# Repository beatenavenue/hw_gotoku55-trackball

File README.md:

English | [日本語](README_ja.md)

> They say the trackball journey ends once you buy a Kensington SlimBlade Pro and an Elecom COMFY wrist rest.  
> But couldn't the case be made smaller?

# GOTOKU-55 Trackball

## What is this?
This is a **"part"** for a 55 mm trackball. To see where it fits, you need some background, in order.

### Ploopy Adept
The Adept is a trackball with a 44 mm ball (1.75 in ≈ 44.5 mm), developed by Ploopy, a small Canadian company. The design files and firmware are open source, but parts you source yourself may not fit dimensionally, so buying a kit or a fully assembled unit from the official Ploopy store is recommended.

- Link: [Adept Trackball](https://ploopy.co/adept-trackball/)

### Anyball
Adept Anyball is a mod project that reworks the Adept case so that the ball rides on BTUs (ball transfer units). By choosing a case variant, you can use anything from a small 34 mm ball up to a 68 mm billiard ball. The files are published on GitHub, and you 3D print and assemble them yourself.

There is of course a 55 mm version, but its supports sit low, so the ball sticks far out of the case and it is not very comfortable to use.

- Link: [Adept Anyball](https://github.com/adept-anyball/)

### small-btu v4 (Slim)
A compact case for 34 mm / 38 mm balls by Fabricio Bastian, published within the Anyball project. It is made as low-profile as possible so that it can sit between the halves of a split keyboard, and its design is beautiful and refined.  
Going by the height of the buttons alone, it is probably lower than the Keychron Nape Pro, one of the smallest trackballs on the market. If you like low-profile keyboards, it is very appealing.

- Link: [adept-anyball/ploopy-adept-small-btu](https://github.com/adept-anyball/ploopy-adept-small-btu)

### GOTOKU-55
Putting a 55 mm ball on small-btu v4 is quite a stretch. The ball itself is large, and arms built for BTUs become huge as well, so it would be almost unusable.  
So, to keep things compact, I made an arm part (the "trackball support" in small-btu terms) that holds a 55 mm ball on the same ball bearings Ploopy uses. That is GOTOKU-55. The name comes from *gotoku* (五徳), the pronged trivet that holds a pot over a Japanese gas burner, which is what the arm part looks like. The 55 is the ball diameter in millimetres.

In most cases the arm part is all you need. The small-btu v4 case is polished and beautiful, so you can use it as is.

### The arm
There are two versions of the arm.

- **One-piece version.** For printing in PLA.
- **Split version.** For metal printing. The arm is metal, and the center floor (the cover over the sensor lens) is a separate PLA part.

A 55 mm ball is heavy, and you roll it with your palm. A PLA arm bends outward under this load. So I recommend printing the arm in metal with SLM (metal 3D printing, for example in stainless steel 316L). With a metal arm, the arm does not bend at all. A metal arm alone is enough to fix this problem.

Use the split version for metal printing. The PLA floor goes in from below. It is held between the metal arm and the sensor lens, so the heavy metal arm does not press on the lens.

### The case
However, with a grip like mine, the stock v4 gets in the way. When I lay my thumb flat to press the front buttons, the corner of the case hits my finger.

So, for people who hold it this way, I also made a modified case that extends the front buttons all the way to the edge.
The screw holes and so on are unchanged from v4, so printing only the top is enough. But the front wall disappears and it looks a little bare, so I made a bottom as well.

## Compatibility
small-btu v4 only.

The arm fits both the original small-btu v4 case and the GOTOKU case.

v5 has a similar shape, so it might work, but by my estimate the ball would probably interfere slightly.

## How to build
See the [build guide](docs/BUILD.md).

## License
Copyright (C) 2026 Kotaro WAJIKI  
Based on ploopy-adept-small-btu v4, Copyright (C) Fabricio Bastian  
Licensed under the GNU General Public License v3.0

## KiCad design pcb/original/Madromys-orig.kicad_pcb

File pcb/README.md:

English | [日本語](README_ja.md)

# GOTOKU PCB v1

This is a modified version of the Ploopy Madromys PCB (R1.001), the main board of the Ploopy Adept trackball.
The goal is to order the board with assembly (PCBA) from JLCPCB, so that no hand soldering is needed for the small parts.

**This is NOT an official Ploopy product. Do not ask Ploopy for support.**

This board is not built and not tested yet.

## This board alone is not a complete trackball

JLCPCB assembles all parts in the BOM except the optical sensor. You need to get these parts yourself and solder the sensor by hand.

- The optical sensor PMW3360DM-T2QU and the lens LM19-LSI

## Variants

There are two variants. They differ only in the USB-C connector.

| Folder | USB-C connector | Notes |
|---|---|---|
| [original](original/) | JAE DX07S016JA1R1500 (LCSC C3197885) | Same connector and routing as the original board. |
| [hro](hro/) | HRO TYPE-C-31-M-12 (LCSC C165948) | Slightly cheaper at JLCPCB. Routing around the connector was changed by hand. |

Each folder has these files:

- `*.kicad_pcb` is the board data for KiCad.
- `*-gerber.zip` is the Gerber and drill data.
- `*-BOM-JLC.csv` and `*-CPL-JLC.csv` are the BOM and the placement file for JLCPCB assembly.
- `*-gerber-preview.png` is a preview image of the Gerber data.

## Ordering at JLCPCB

- 4 layers, 0.8 mm thickness
- Assemble top side
- Upload the BOM and the CPL file of the same variant.

The optical sensor (PMW3360DM-T2QU) has no LCSC number in the BOM, so JLCPCB does not assemble it.

The package of the switch D2LS-21 (LCSC C3823622) is not listed on the JLCPCB part page. Check the position and the direction of the switches in the placement preview before you order.

## Changes from the original

The original data is the Altium project in [ploopyco/adept-trackball](https://github.com/ploopyco/adept-trackball) (`hardware/electronics/PCBs/Madromys`, commit `2ec4576`).
Only the PCB was converted. The schematic was not converted. See the original schematic PDF for the circuit.

### Conversion from Altium to KiCad

The board was converted with the Altium importer of KiCad 7.
These fixes were needed after the conversion.

- The square opening for the optical sensor is now a cutout in the board outline.
- The two locating holes of the USB-C connector are now non-plated holes.
- 10 very short broken arcs in the copper were replaced with straight segments.
- The board thickness is set to 0.8 mm. This value comes from the Altium layer stack.

### Parts that are not mounted

These parts are marked as "DNP" (do not populate). They are removed from the BOM and the CPL file. Their pads stay on the board.

| Designator | Part | Reason |
|---|---|---|
| LED.D.1, LED.D.3 | Addressable RGB LED | See "Why the LEDs were removed" below. |
| LED.C.20, LED.C.23, LED.R.9, LED.R.16 | Capacitors and resistors for the LEDs | Not needed without the LEDs. |
| USB.R.12, USB.R.14 | 10k resistor on CC1 and CC2 | The original uses two 10k resistors in parallel on each CC line. This board uses one 5.1k resistor instead. |
| MCU.J.1 | 2-pin header | No header is mounted, same as the original product. The two holes are used to start the bootloader. See below. |

### Why the LEDs were removed

- The official firmware does not enable the LED feature (rgblight). The configuration file still has settings for 3 LEDs and for animations, so an illumination feature may have been planned. The board has only 2 LEDs.
- The LEDs run on 5 V (V_USB), but the data signal comes from the RP2040 at 3.3 V. This leaves only a small margin to the voltage that this type of LED needs to read a high level, so the LEDs may not work as expected.
- The removed parts are all cheap, so removing them does not reduce the cost much.

### Changed values and substitute parts

| Designator | Original | This board |
|---|---|---|
| USB.R.13, USB.R.15 | 10k 1% | 5.1k 1% (one resistor for each CC line) |
| USB.Z.1 | IP4220CZ6 (ESD protection) | SRV05-4 (LCSC C384887). Same pinout. |
| REG.U.4 | AP2204K-1.8 | AP2112K-1.8 (LCSC C176944). Same pinout. |
| MCU.Y.1 | RH100-12.000-16-3030 (12 MHz, 16 pF) | X322512MSB4SI (12 MHz, 20 pF, LCSC C9002). The load capacitors stay at 18 pF. |

REG.C.15 (100 pF) is marked as "not fitted" in the BoM variant of the original project.
On this board it is mounted.

Other passive parts were replaced with common LCSC parts of the same value and size.

### Silkscreen

- The board name "Madromys R1.001 / August 2023" was changed to "GOTOKU PCB v1".
- The label "MCH.FID.1" was hidden.
- A logo and a notice of the modification were added on the top side.

### Holes for an extra button (GP12)

Two plated holes were added above LED.D.1, the LED on the upper right of the optical sensor.
They are marked "GP12" and "GND" on the silkscreen. The pitch is 2.54 mm.

- GP12 (square pad) is connected to GPIO12 of the RP2040. This was the data line for the LEDs (LEDData). It is free because the LEDs are not mounted.
- GND (round pad) is connected to the ground planes.

Connect a switch between the two holes.

**This button does not work with the official Ploopy QMK firmware, even without the LEDs.**
The official firmware does not read GP12.
To use the button, build your own firmware. Add GP12 to the direct pins of the matrix, and add a key for it to the layout and the keymap.

Do not use this button if you mount the LEDs. They use the same pin.

### HRO variant only

The HRO connector has a different pad layout. These changes were made only in the `hro` variant.

- The connector footprint was replaced with `USB_C_Receptacle_HRO_TYPE-C-31-M-12` from the KiCad library. The position and the direction are the same as the original connector.
- The D+, D-, CC1, CC2 and VBUS traces near the connector were changed to fit the new pads.
- One VBUS via was moved, and one GND via under the connector was removed.
- The copper pour was cleared around the new traces and pads.

The connections and the clearances near the connector were checked with a script.
**A full DRC has not been run yet. Run the DRC in KiCad 8 or later before you order this variant.**
`Madromys-usb-area-orig-vs-hro.png` shows the area around the connector in both variants.

## Starting the bootloader

You do not need this for the first firmware upload.
A new board has an empty flash memory, so the RP2040 starts in the bootloader (BOOTSEL mode) automatically.

To update the firmware later, hold the bottom left button (matrix [0,0]) while you plug in the USB cable.

If the firmware is broken and the button does not work, use the two holes of MCU.J.1 near LED.D.3.
Connect the two holes with metal tweezers, and plug in the USB cable at the same time.
One hole is GND. The other hole is connected to the chip select line of the flash memory through a 1k resistor.

## License

The files in this folder are licensed under the CERN Open Hardware Licence Version 2, Strongly Reciprocal (CERN-OHL-S-2.0).
See [LICENSE](LICENSE).
This is different from the rest of this repository, which uses GPL-3.0.

- Original design: Ploopy Madromys R1.001 (Ploopy Adept) by Ploopy Corporation, licensed under CERN-OHL-S-2.0.
  Source: https://github.com/ploopyco/adept-trackball
- Modifications: Copyright (C) 2026 Kotaro WAJIKI. Modified on 2026-10-11. The changes are listed in "Changes from the original" above.
- Source Location of this modified design: https://github.com/beatenavenue/hw_gotoku55-trackball/tree/main/pcb

This design is provided "as is", without any warranty. See section 6 of the license.

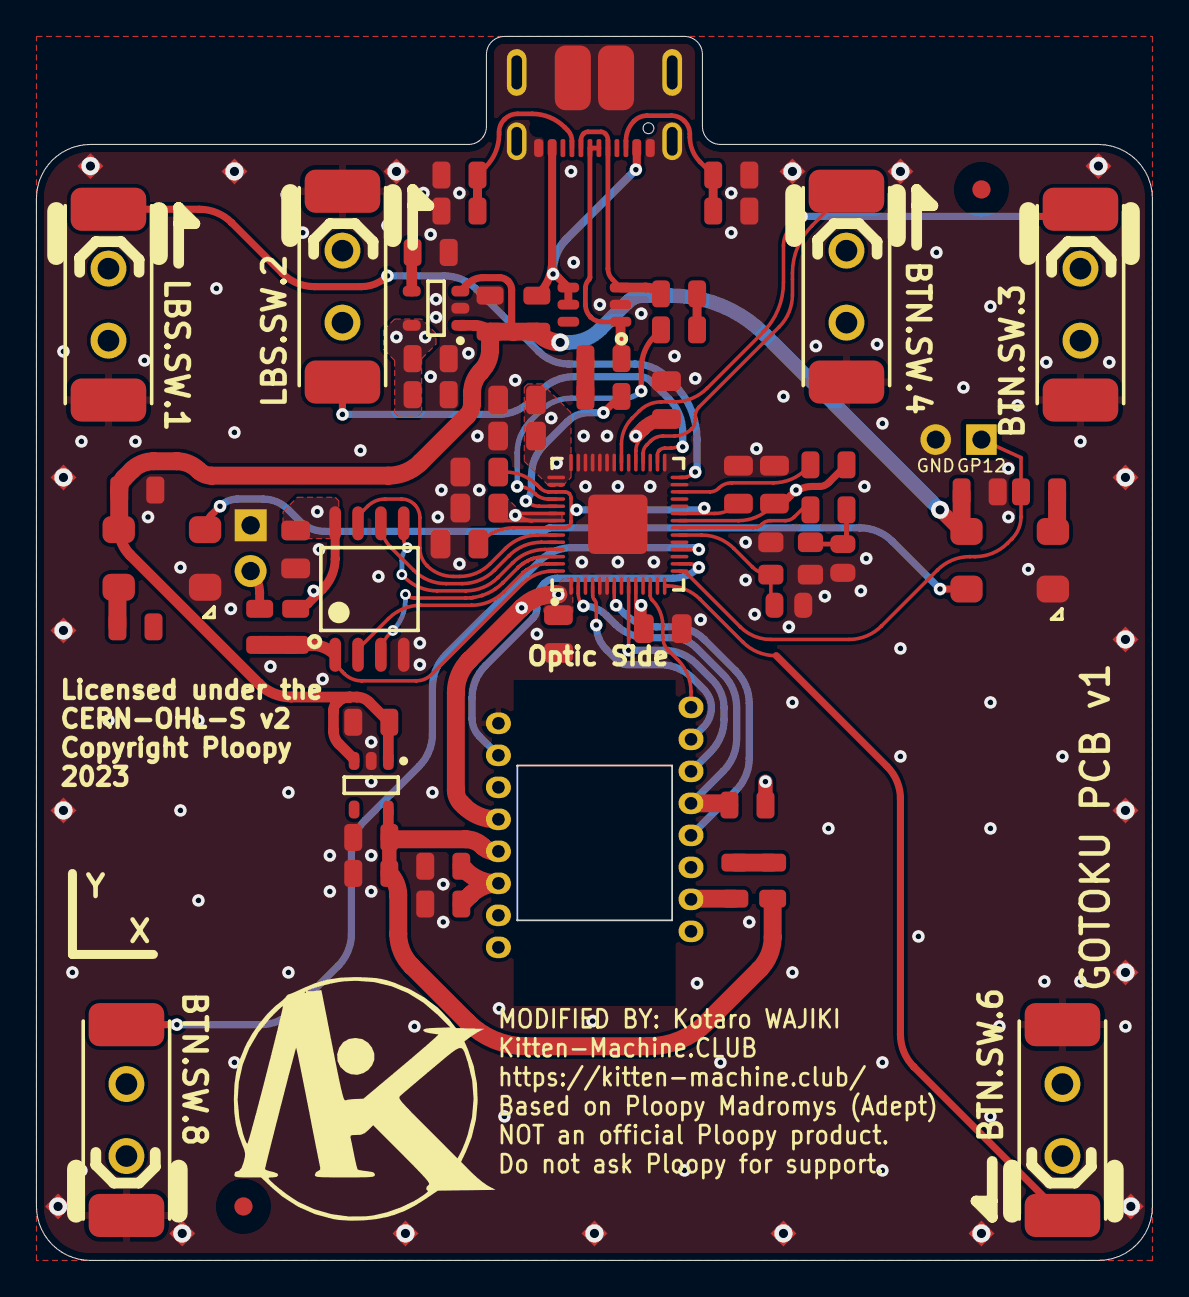
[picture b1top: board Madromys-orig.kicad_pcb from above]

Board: 4 copper layers, 62.0 x 68.0 mm, 84 parts (1 on the bottom side), 45 nets.

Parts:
BTN.J.9: EXT BUTTON; EXT_BUTTON_2x1
BTN.SW.3, BTN.SW.4, BTN.SW.6, BTN.SW.8: D2LS-21
KM.LOGO.1: KM_LOGO
LBS.SW.1, LBS.SW.2: D2LS-21
LED.C.20, LED.C.23, LED.R.9, LED.R.16: DNP 0805; 0805
LED.D.1, LED.D.3: DNP IN-PI55TATPRPGPB; IN-PI55TATPRPGPB
MCH.FID.1, MCH.FID.2: IPC-7351 Fiducial 1mm; FIDUCIAL_1.5
MCH.LOGO.2: Coordinate system marker for assembly; Coordinate System
MCH.SP.1, MCH.SP.2, MCH.SP.3, MCH.SP.4, MCH.SP.5, MCH.SP.6, MCH.SP.7, MCH.SP.8, MCH.SP.9, MCH.SP.10, MCH.SP.11, MCH.SP.12, MCH.SP.13, MCH.SP.14, MCH.SP.15, MCH.SP.16, MCH.SP.17, MCH.SP.18, MCH.SP.19, MCH.SP.20: Spark Gap; SparkGap
MCU.C.1, MCU.C.2, MCU.C.3, MCU.C.4, MCU.C.5, MCU.C.6, MCU.C.7, MCU.C.8, MCU.C.21, MCU.C.22, MCU.C.24: 0805 X5R; 0805 - TALL
MCU.C.9, MCU.C.19: 0603
MCU.J.1: DNP HEADER2; 2x1
MCU.R.1, MCU.R.2, MCU.R.11, MCU.R.17: 0805
MCU.U.1: W25Q16JVSSIQ; W25Q128JVS - SOIC127P790X216-8M
MCU.U.5: RP2040; RP2040 - QFN40P700X700X90_HS-57M
MCU.Y.1: RH100-12.000-16-3030
MOS.C.10, MOS.C.11, MOS.R.3, MOS.R.4, MOS.R.5: 0805
MOS.U.2: PMW3360DM-T2QU
REG.C.12, REG.C.13, REG.C.14, REG.C.15, REG.C.16, REG.C.17, REG.C.18: 0805
REG.U.3: AP2202K-3.3; AP2202 - SOT95P270X145-5N
REG.U.4: AP2204K-1.8; AP2202 - SOT95P270X145-5N
USB.FB.1, USB.FB.2, USB.FB.3: ACML-0805-601-T; 0805
USB.J.3: DX07S016JA1R1500
USB.R.6, USB.R.7: 0805
USB.R.12, USB.R.14: DNP 0805; 0805
USB.R.13, USB.R.15: 5.1k 1%; 0805
USB.Z.1: IP4220CZ6,125; PESD3V3S4UD - SOT95P275X110-6N

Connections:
1V1: MCU.C.21.2, MCU.C.22.2, MCU.C.24.2, MCU.U.5.23, MCU.U.5.45, MCU.U.5.50
1V8: MOS.R.3.2, MOS.U.2.4, REG.C.17.2, REG.C.18.2, REG.U.4.5
3V3: MCU.C.1.2, MCU.C.2.2, MCU.C.3.2, MCU.C.4.2, MCU.C.5.2, MCU.C.6.2, MCU.C.7.2, MCU.C.8.2, MCU.R.2.1, MCU.R.17.1, MCU.U.1.8, MCU.U.5.1, MCU.U.5.10, MCU.U.5.22, MCU.U.5.33, MCU.U.5.42, MCU.U.5.43, MCU.U.5.44, MCU.U.5.48, MCU.U.5.49, MOS.R.5.2, MOS.U.2.5, REG.C.13.2, REG.C.14.2, REG.U.3.5
GND: BTN.J.9.2, BTN.SW.3.B, BTN.SW.4.B, BTN.SW.6.B, BTN.SW.8.A, LBS.SW.1.B, LBS.SW.2.A, LED.C.20.1, LED.C.23.1, LED.D.1.3, LED.D.3.3, MCH.SP.1.1, MCH.SP.2.1, MCH.SP.3.1, MCH.SP.4.1, MCH.SP.5.1, MCH.SP.6.1, MCH.SP.7.1, MCH.SP.8.1, MCH.SP.9.1, MCH.SP.10.1, MCH.SP.11.1, MCH.SP.12.1, MCH.SP.13.1, MCH.SP.14.1, MCH.SP.15.1, MCH.SP.16.1, MCH.SP.17.1, MCH.SP.18.1, MCH.SP.19.1, MCH.SP.20.1, MCU.C.1.1, MCU.C.2.1, MCU.C.3.1, MCU.C.4.1, MCU.C.5.1, MCU.C.6.1, MCU.C.7.1, MCU.C.8.1, MCU.C.9.2, MCU.C.19.1, MCU.C.21.1, MCU.C.22.1, MCU.C.24.1, MCU.J.1.1, MCU.U.1.4, MCU.U.5.3, MCU.U.5.5, MCU.U.5.6, MCU.U.5.8, MCU.U.5.11, MCU.U.5.13, MCU.U.5.17, MCU.U.5.19, MCU.U.5.27, MCU.U.5.29, MCU.U.5.31, MCU.U.5.34, MCU.U.5.36, MCU.U.5.37, MCU.U.5.38, MCU.U.5.39, MCU.U.5.40, MCU.U.5.41, MCU.U.5.57, MCU.Y.1.2, MCU.Y.1.4, MOS.C.10.1, MOS.C.11.1, MOS.U.2.8, REG.C.12.1, REG.C.13.1, REG.C.14.1, REG.C.15.1, REG.C.16.1, REG.C.17.1, REG.C.18.1, REG.U.3.2, REG.U.4.2, USB.J.3.1, USB.J.3.12, USB.J.3.SHELL, USB.R.12.1, USB.R.13.1, USB.R.14.1, USB.R.15.1, USB.Z.1.2
LEDData: BTN.J.9.1, LED.R.16.2, MCU.U.5.15
NetBTN.SW.3_A: BTN.SW.3.A, MCU.U.5.35
NetBTN.SW.4_A: BTN.SW.4.A, MCU.U.5.32
NetBTN.SW.6_A: BTN.SW.6.A, MCU.U.5.14
NetBTN.SW.8_B: BTN.SW.8.B, MCU.U.5.18
NetLBS.SW.1_A: LBS.SW.1.A, MCU.U.5.28
NetLBS.SW.2_B: LBS.SW.2.B, MCU.U.5.30
NetLED.D.1_2: LED.D.1.2, LED.D.3.4
NetLED.D.1_4: LED.D.1.4, LED.R.16.1
NetLED.D.3_2: LED.D.3.2, LED.R.9.2
NetMCU.C.9_1: MCU.C.9.1, MCU.U.5.20, MCU.Y.1.1
NetMCU.C.19_2: MCU.C.19.2, MCU.R.11.2, MCU.Y.1.3
NetMCU.J.1_2: MCU.J.1.2, MCU.R.1.1
NetMCU.R.1_2: MCU.R.1.2, MCU.R.2.2, MCU.U.1.1, MCU.U.5.56
NetMCU.R.11_1: MCU.R.11.1, MCU.U.5.21
NetMCU.R.17_2: MCU.R.17.2, MCU.U.5.26
NetMCU.U.1_2: MCU.U.1.2, MCU.U.5.55
NetMCU.U.1_3: MCU.U.1.3, MCU.U.5.54
NetMCU.U.1_5: MCU.U.1.5, MCU.U.5.53
NetMCU.U.1_6: MCU.U.1.6, MCU.U.5.52
NetMCU.U.1_7: MCU.U.1.7, MCU.U.5.51
NetMCU.U.5_2: MCU.U.5.2, MOS.R.5.1, MOS.U.2.12
NetMCU.U.5_4: MCU.U.5.4, MOS.U.2.10
NetMCU.U.5_7: MCU.U.5.7, MOS.U.2.13
NetMCU.U.5_9: MCU.U.5.9, MOS.U.2.11
NetMCU.U.5_12: MCU.U.5.12, MOS.U.2.9
NetMCU.U.5_16: MCU.U.5.16, MOS.U.2.7
NetMCU.U.5_46: MCU.U.5.46, USB.R.6.2
NetMCU.U.5_47: MCU.U.5.47, USB.R.7.2
NetMOS.C.10_2: MOS.C.10.2, MOS.C.11.2, MOS.U.2.3
NetMOS.R.3_1: MOS.R.3.1, MOS.R.4.2
NetMOS.R.4_1: MOS.R.4.1, MOS.U.2.15
NetREG.C.15_2: REG.C.15.2, REG.U.3.4
NetUSB.FB.1_1: USB.FB.1.1, USB.J.3.2, USB.J.3.11, USB.Z.1.4, USB.Z.1.5
NetUSB.FB.2_1: USB.FB.2.1, USB.J.3.5, USB.J.3.8, USB.Z.1.3
NetUSB.FB.2_2: USB.FB.2.2, USB.R.6.1
NetUSB.FB.3_1: USB.FB.3.1, USB.J.3.6, USB.J.3.7, USB.Z.1.1
NetUSB.FB.3_2: USB.FB.3.2, USB.R.7.1
NetUSB.J.3_3: USB.J.3.3, USB.R.14.2, USB.R.15.2
NetUSB.J.3_9: USB.J.3.9, USB.R.12.2, USB.R.13.2
V_USB: LED.C.20.2, LED.C.23.2, LED.D.1.1, LED.D.3.1, REG.C.12.2, REG.C.16.2, REG.U.3.1, REG.U.3.3, REG.U.4.1, REG.U.4.3, USB.FB.1.2

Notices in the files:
pcb/original/Madromys-orig.kicad_pcb:
CERN-OHL-S v2
Copyright Ploopy
